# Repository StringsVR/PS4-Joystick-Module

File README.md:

* Basic PS4 Joystick PCB for Arduino/Pi *

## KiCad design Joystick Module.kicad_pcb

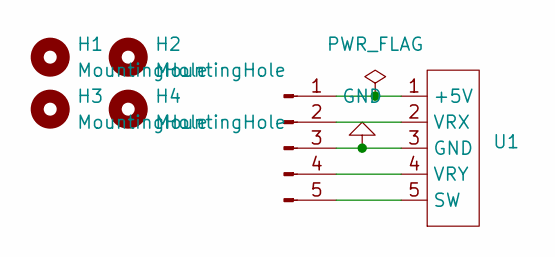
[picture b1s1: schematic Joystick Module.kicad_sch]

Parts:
H1, H2, H3, H4: MountingHole; MountingHole_2.2mm_M2
J1: Conn_01x05_Pin; PinHeader_1x05_P1.27mm_Vertical
U1: PS4_Joystick

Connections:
GND: J1.3, U1.3 (GND)
unnamed: J1.1, U1.1 (+5V)
unnamed: J1.2, U1.2 (VRX)
unnamed: J1.4, U1.4 (VRY)
unnamed: J1.5, U1.5 (SW)

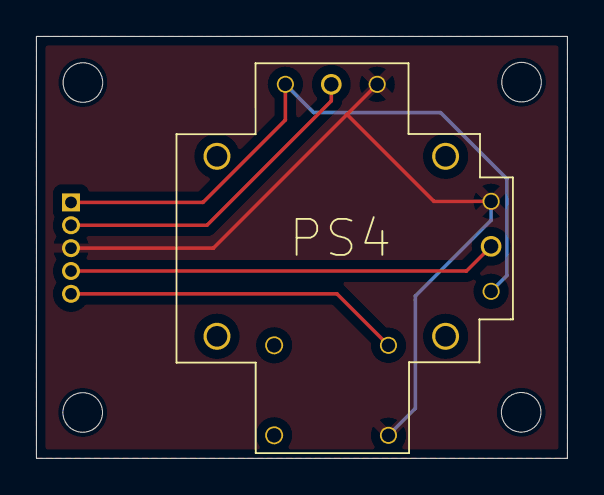
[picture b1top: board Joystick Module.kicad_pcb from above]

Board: 2 copper layers, 29.5 x 23.4 mm, 6 parts (1 on the bottom side), 5 nets.
